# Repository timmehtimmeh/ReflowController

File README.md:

# TimmehTimmeh's Arduino Board

This repository contains support for the following TimmehTimmeh Arduino-compatible reflow oven controller.  The reflow controller runs on an Atmega32u4 at 3.3V/8MHz.

# Attributions
This project is based on TMK's headless reflow oven (https://github.com/tmk/HeadlessReflowOven) which is in turn based on  work of 

* [ohararp ReflowOven]  (https://github.com/ohararp/ReflowOven)

* which is modification of [rocketscream Reflow-Oven-Controller]  (https://github.com/rocketscream/Reflow-Oven-Controller)

rocketscream released the work under Creative Commons Share Alike v3.0 license.

The bootloader and corresponding installation instructions are a modification of Sparkfun's bootloader code for their Arduino Pro Micro: (https://github.com/sparkfun/Arduino_Boards)

The directory structure is as follows:
* [ReflowBoard]	- The firmware, bootloader, and arduino IDE files that communicate with the board
* [ReflowOven]	- The software (arduino software project) that runs on the board
* [Schematics] - schematics and eagle files for the board
* [libraries] - Library files that the arduino project links against

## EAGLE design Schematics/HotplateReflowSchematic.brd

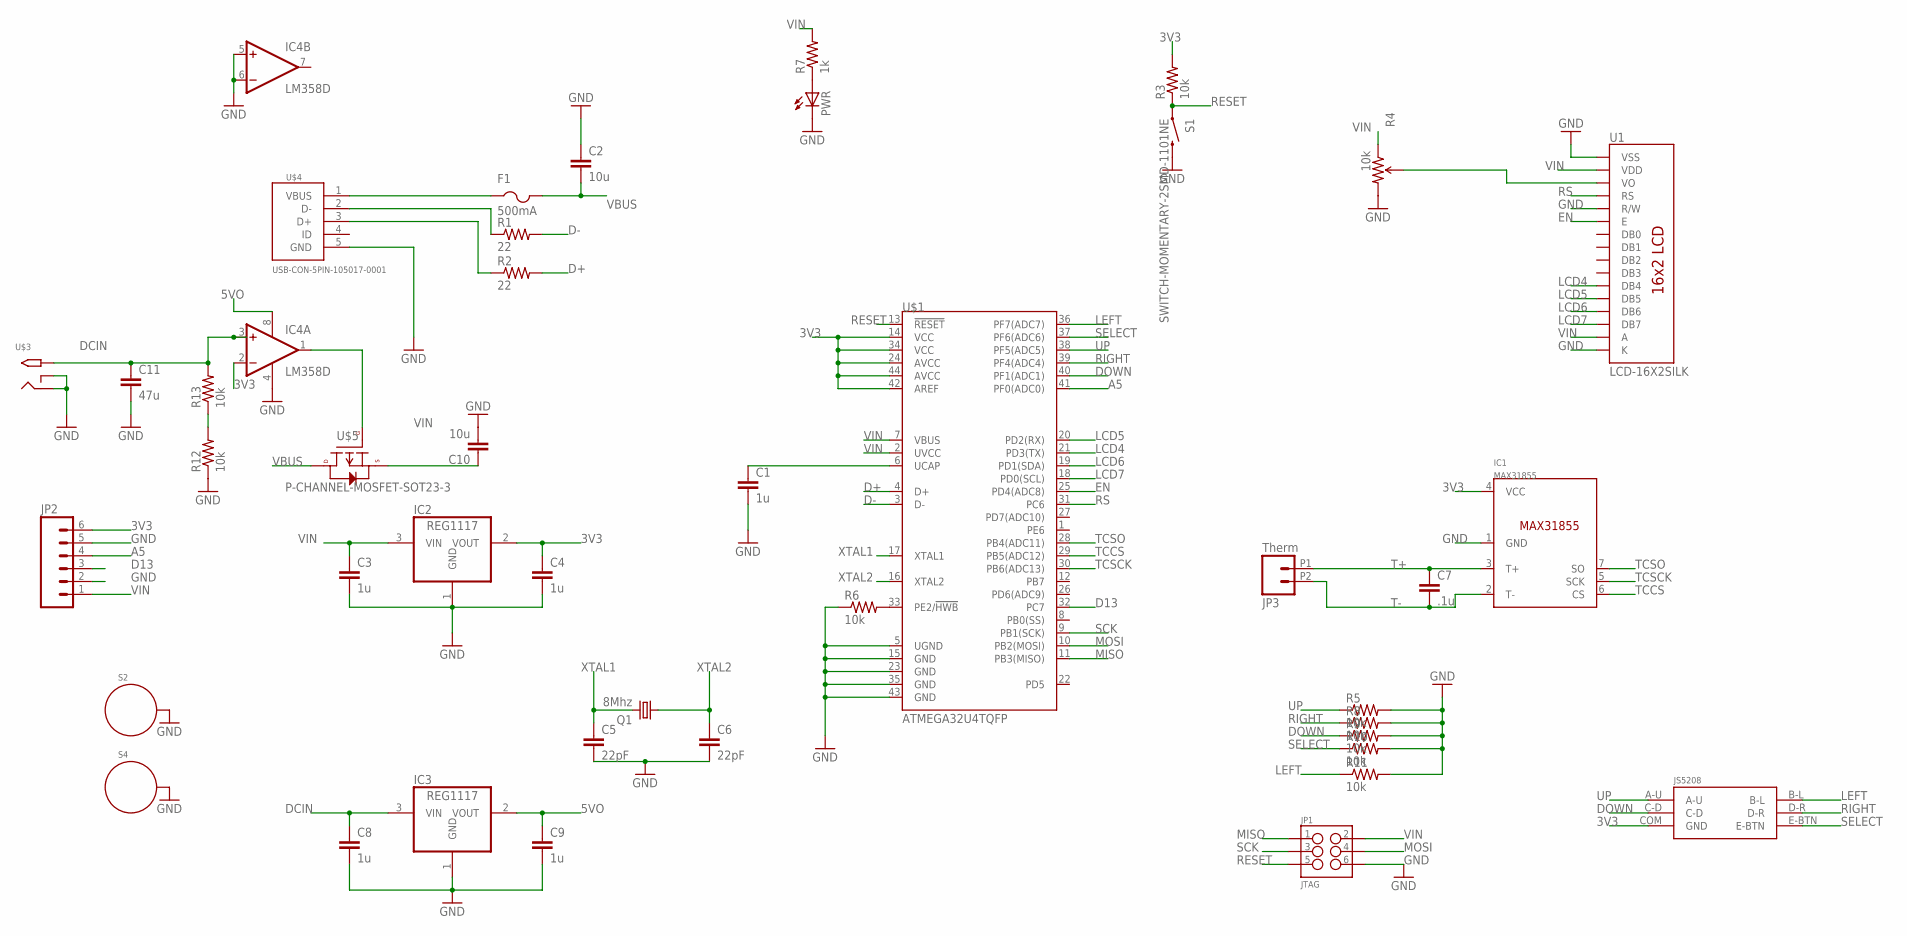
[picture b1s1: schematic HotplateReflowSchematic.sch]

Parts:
C1, C3, C4, C8, C9: 1u; 0603-CAP
C2, C10: 10u; 0603-CAP
C5, C6: 22pF; 0603-CAP
C7: .1u; 0603-CAP
C11: 47u; 0603-CAP
F1: 500mA; 1812
IC1: MAX31855; SOIC8
IC2, IC3: REG1117; SOT223
IC4: LM358D; SO08
JP1: JTAG; 2X3-SHROUDED
JP2: M06LOCK; 1X06_LOCK
JP3: Therm; 1X02_2.54_SCREWTERM
PWR: LEDCHIP-LED0603; CHIP-LED0603
Q1: 8Mhz; HC49UP
R1, R2: 22; 0603-RES
R3, R5, R6, R8, R9, R10, R11, R12, R13: 10k; 0603-RES
R4: 10k; TRIMPOT-5MM-V2
R7: 1k; 0603-RES
S1: SWITCH-MOMENTARY-2SMD-1101NE; TACTILE-SWITCH-1101NE
S2, S4: STANDOFF_ELECTRICAL; STANDOFF-ELECTRICAL
U1: LCD-16X2SILK; LCD-16X2
U$1: ATMEGA32U4TQFP; SPARKFUN-DIGITALIC_TQFP44
U$2: JS5208; JS5208_PKG
U$3: 2.1MMJACKTHM; PJ-102A
U$4: USB-CON-5PIN-105017-0001; USB-MICRO-MOLEX-105017-0001
U$5: P-CHANNEL-MOSFET-SOT23-3; SOT23-3

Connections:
3V3: C4.1, IC1.4 (VCC), IC2.2 (VOUT), IC4.2 (-IN), JP2.6, R3.2, U$1.14 (VCC), U$1.24 (AVCC), U$1.34 (VCC), U$1.42 (AREF), U$1.44 (AVCC), U$2.COM (GND)
5VO: C9.1, IC3.2 (VOUT), IC4.8 (V+)
A5: JP2.4, U$1.41 (PF0(ADC0))
D13: JP2.3, U$1.32 (PC7)
D+: R2.2, U$1.4 (D+)
D-: R1.2, U$1.3 (D-)
DCIN: C8.1, C11.1, IC3.3 (VIN), IC4.3 (+IN), R13.2, U$3.TIP
DOWN: R9.1, U$1.40 (PF1(ADC1)), U$2.C-D
EN: U1.6 (E), U$1.25 (PD4(ADC8))
GND: C1.2, C2.1, C3.2, C4.2, C5.2, C6.2, C8.2, C9.2, C10.2, C11.2, IC1.1 (GND), IC2.1 (GND), IC3.1 (GND), IC4.4 (V-), IC4.5 (+IN), IC4.6 (-IN), JP1.6, JP2.2, JP2.5, PWR.C, R4.C (CW), R5.2, R6.1, R8.2, R9.2, R10.2, R11.2, R12.1, S1.2, S2.P1, S4.P1, U1.1 (VSS), U1.5 (R/W), U1.16 (K), U$1.5 (UGND), U$1.15 (GND), U$1.23 (GND), U$1.35 (GND), U$1.43 (GND), U$3.RING, U$3.RING_SW, U$4.5 (GND)
LCD4: U1.11 (DB4), U$1.21 (PD3(TX))
LCD5: U1.12 (DB5), U$1.20 (PD2(RX))
LCD6: U1.13 (DB6), U$1.19 (PD1(SDA))
LCD7: U1.14 (DB7), U$1.18 (PD0(SCL))
LEFT: R11.1, U$1.36 (PF7(ADC7)), U$2.B-L
MISO: JP1.1, U$1.11 (PB3(MISO))
MOSI: JP1.4, U$1.10 (PB2(MOSI))
unnamed: R4.B (WIPER), U1.3 (VO)
unnamed: F1.1, U$4.1 (VBUS)
unnamed: R1.1, U$4.2 (D-)
unnamed: R2.1, U$4.3 (D+)
unnamed: C1.1, U$1.6 (UCAP)
unnamed: PWR.A, R7.1
unnamed: R6.2, U$1.33 (PE2/!HWB)
unnamed: R12.2, R13.1
unnamed: IC4.1 (OUT), U$5.1 (G)
RESET: JP1.5, R3.1, S1.1, U$1.13 (!RESET)
RIGHT: R8.1, U$1.39 (PF4(ADC4)), U$2.D-R
RS: U1.4 (RS), U$1.31 (PC6)
SCK: JP1.3, U$1.9 (PB1(SCK))
SELECT: R10.1, U$1.37 (PF6(ADC6)), U$2.E-BTN
T+: C7.1, IC1.3 (T+), JP3.P1 (1)
T-: C7.2, IC1.2 (T-), JP3.P2 (2)
TCCS: IC1.6 (CS), U$1.29 (PB5(ADC12))
TCSCK: IC1.5 (SCK), U$1.30 (PB6(ADC13))
TCSO: IC1.7 (SO), U$1.28 (PB4(ADC11))
UP: R5.1, U$1.38 (PF5(ADC5)), U$2.A-U
VBUS: C2.2, F1.2, U$5.3 (D)
VIN: C3.1, C10.1, IC2.3 (VIN), JP1.2, JP2.1, R4.A (CCW), R7.2, U1.2 (VDD), U1.15 (A), U$1.2 (UVCC), U$1.7 (VBUS), U$5.2 (S)
XTAL1: C5.1, Q1.2, U$1.17 (XTAL1)
XTAL2: C6.1, Q1.1, U$1.16 (XTAL2)

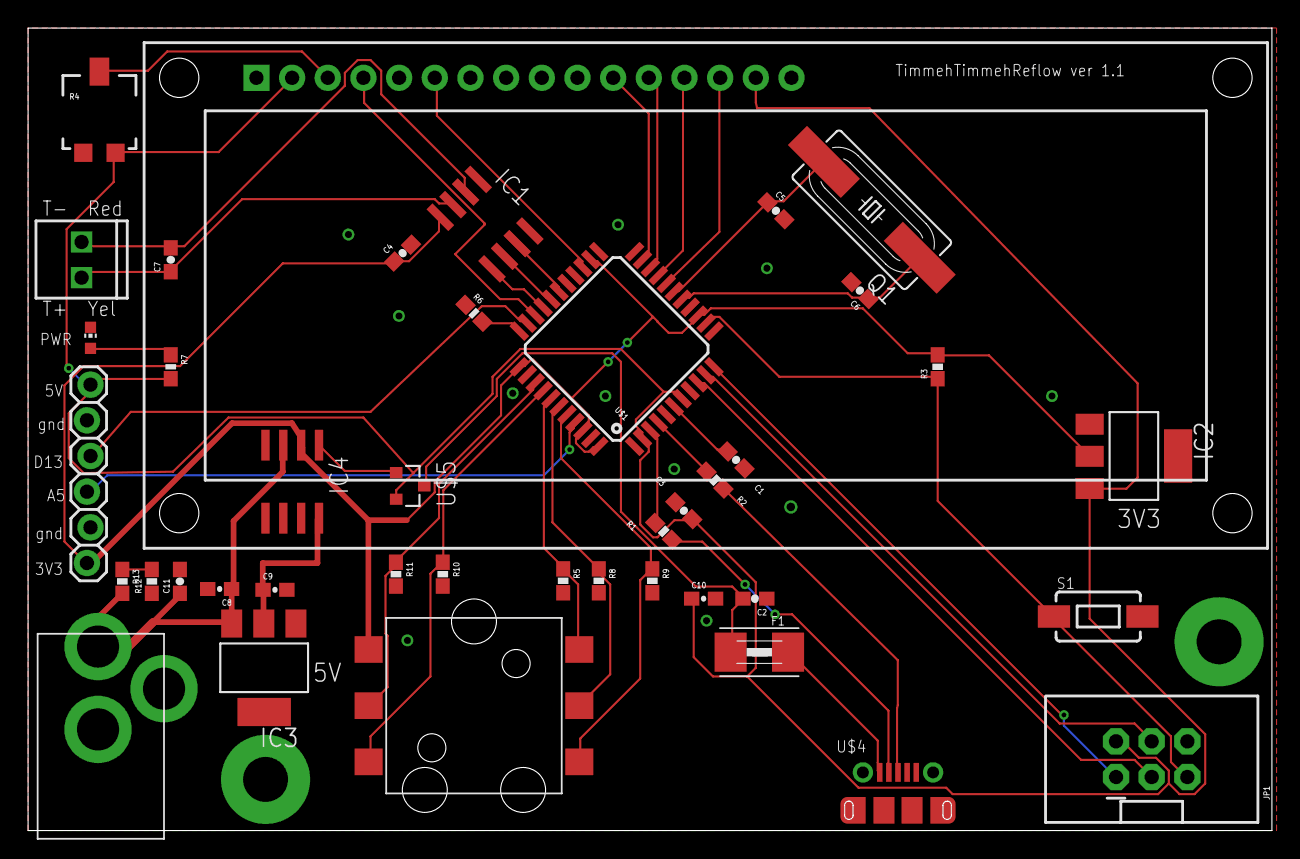
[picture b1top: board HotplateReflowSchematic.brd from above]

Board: 2 copper layers, 88.6 x 57.1 mm, 43 parts (0 on the bottom side), 41 nets.

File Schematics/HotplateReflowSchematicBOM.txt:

Partlist exported from C:/Users/timme/Documents/Arduino/ReflowController/Schematics/HotplateReflowSchematic.sch at 6/29/2016 9:49 PM

Qty Value                        Device                       Package                     Parts                              Description                                                                              MF MPN     OC_FARNELL OC_NEWARK PROD_ID   
1                                LEDCHIP-LED0603              CHIP-LED0603                PWR                                LED                                                                                                                                
1                                M06LOCK                      1X06_LOCK                   JP2                                Header 6                                                                                                                           
1   .1u                          CAP0603-CAP                  0603-CAP                    C7                                 Capacitor                                                                                                                          
1   10k                          RESISTOR0603                 0603-RES                    R6                                 Resistor                                                                                                                           
8   10k                          RESISTOR0603-RES             0603-RES                    R3, R5, R8, R9, R10, R11, R12, R13 Resistor                                                                                                                           
1   10k                          TRIMPOT                      TRIMPOT-5MM-V2              R4                                 Various small potentiometers for "set-and-forget" applications                                                                     
2   10u                          CAP0603-CAP                  0603-CAP                    C2, C10                            Capacitor                                                                                                                          
1   1k                           RESISTOR0603                 0603-RES                    R7                                 Resistor                                                                                                                           
5   1u                           CAP0603-CAP                  0603-CAP                    C1, C3, C4, C8, C9                 Capacitor                                                                                                                          
1   2.1MMJACKTHM                 2.1MMJACKTHM                 PJ-102A                     U$3                                2.1mm x 5.5mm THM DC jack with internal switch. Digikey part #PJ-102A, 4UCON part #05537                                           
2   22                           RESISTOR0603-RES             0603-RES                    R1, R2                             Resistor                                                                                                                           
2   22pF                         CAP0603-CAP                  0603-CAP                    C5, C6                             Capacitor                                                                                                                          
1   47u                          CAP0603-CAP                  0603-CAP                    C11                                Capacitor                                                                                                                          
1   500mA                        PTCFUSE-1812                 1812                        F1                                 PTC fuses, resettable thermistors                                                                                                  
1   8Mhz                         CRYSTALHC49UP                HC49UP                      Q1                                 CRYSTAL                                                                                             unknown    unknown             
1   ATMEGA32U4TQFP               ATMEGA32U4TQFP               SPARKFUN-DIGITALIC_TQFP44   U$1                                Atmel 44-pin 8-bit Microcontroller with 32KBytes of ISP Flash and USB Controller -----                                   IC-11161  
1   JS5208                       JS5208                       JS5208_PKG                  U$2                                                                                                                                                                   
1   JTAG                         M03X2SHROUD                  2X3-SHROUDED                JP1                                2x3 .1" header.                                                                                                          CONN-10681
1   LCD-16X2SILK                 LCD-16X2SILK                 LCD-16X2                    U1                                 Standard text-only 16x2 parallel input LCD                                                                                         
1   LM358D                       LM358D                       SO08                        IC4                                OP AMP also LM158; LM258; LM2904                                                                                                   
1   MAX31855                     MAX31855                     SOIC8                       IC1                                                                                                                                                                   
1   P-CHANNEL-MOSFET-SOT23-3     P-CHANNEL-MOSFET-SOT23-3     SOT23-3                     U$5                                P-Channel MOSFET Mode Field Effect Transistor                                                                                      
2   REG1117                      REG1117                      SOT223                      IC2, IC3                           800mA and 1A Low Dropout (LDO) Positive Regulator                                           REG1117 1097566    14P6981             
2   STANDOFF_ELECTRICAL          STANDOFF_ELECTRICAL          STANDOFF-ELECTRICAL         S2, S4                             A standoff intended to be an electrically connected point.                                                                         
1   SWITCH-MOMENTARY-2SMD-1101NE SWITCH-MOMENTARY-2SMD-1101NE TACTILE-SWITCH-1101NE       S1                                 Various NO switches- pushbuttons, reed, etc                                                                              SWCH-00815
1   Therm                        M022.54MM_SCREWTERM          1X02_2.54_SCREWTERM         JP3                                Standard 2-pin 0.1" header. Use with                                                                                               
1   USB-CON-5PIN-105017-0001     USB-CON-5PIN-105017-0001     USB-MICRO-MOLEX-105017-0001 U$4                                Molex Micro USB 105017-0001

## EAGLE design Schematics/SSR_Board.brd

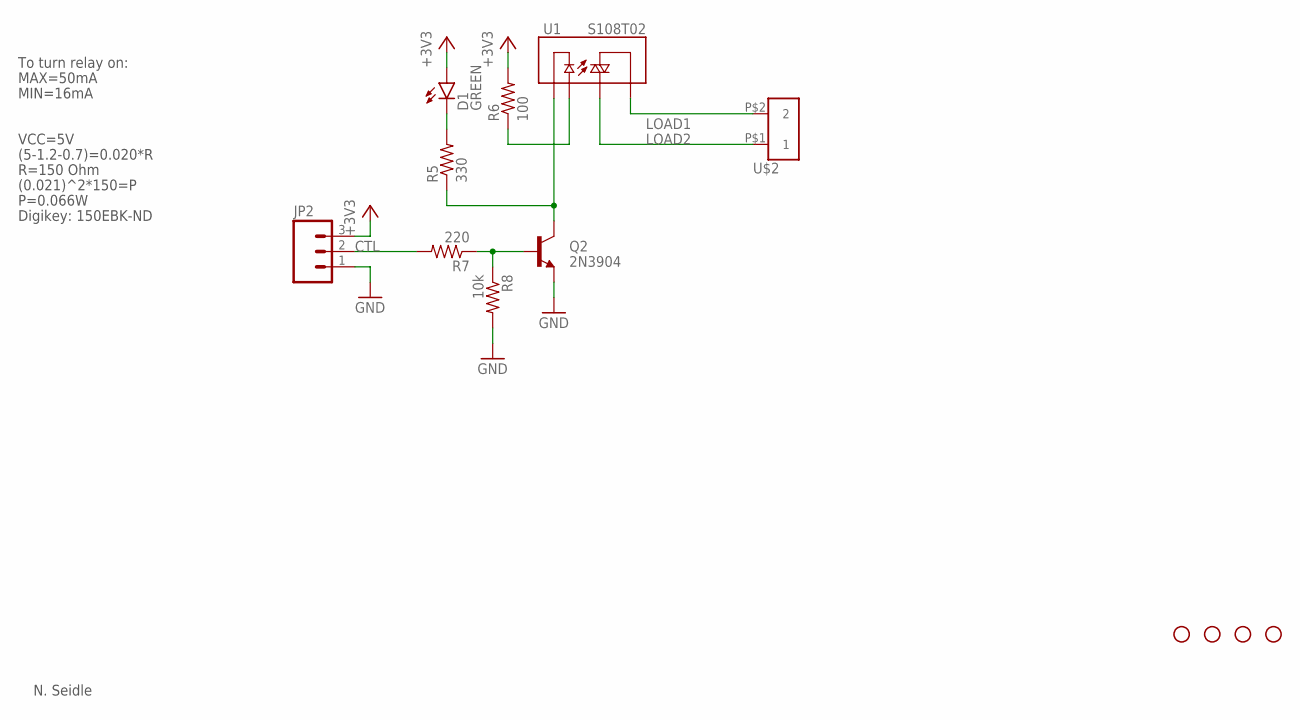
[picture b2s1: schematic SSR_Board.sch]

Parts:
D1: GREEN; LED-0603
JP2: M03SCREW; SCREWTERMINAL-3.5MM-3
Q2: 2N3904; SOT23-3
R5: 330; 0603-RES
R6: 100; 0603-RES
R7: 220; 0603-RES
R8: 10k; 0603-RES
U1: S108T02; RELAY-S108T02
U$2: 6PCV-02-006
U$3, U$4, U$5, U$7: STAND-OFF

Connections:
+3V3: D1.A, JP2.3, R6.2
COIL: Q2.3 (C), R5.1, U1.4 (-)
CTL: JP2.2, R7.2
GND: JP2.1, Q2.2 (E), R8.2
LOAD1: U1.1 (T1), U$2.P$2 (2)
LOAD2: U1.2 (T2), U$2.P$1 (1)
unnamed: R6.1, U1.3 (+)
unnamed: Q2.1 (B), R7.1, R8.1
unnamed: D1.C, R5.2

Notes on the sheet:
N. Seidle
To turn relay on:
(5-1.2-0.7)=0.020*R
R=150 Ohm
VCC=5V
MAX=50mA
MIN=16mA
(0.021)^2*150=P
P=0.066W
Digikey: 150EBK-ND

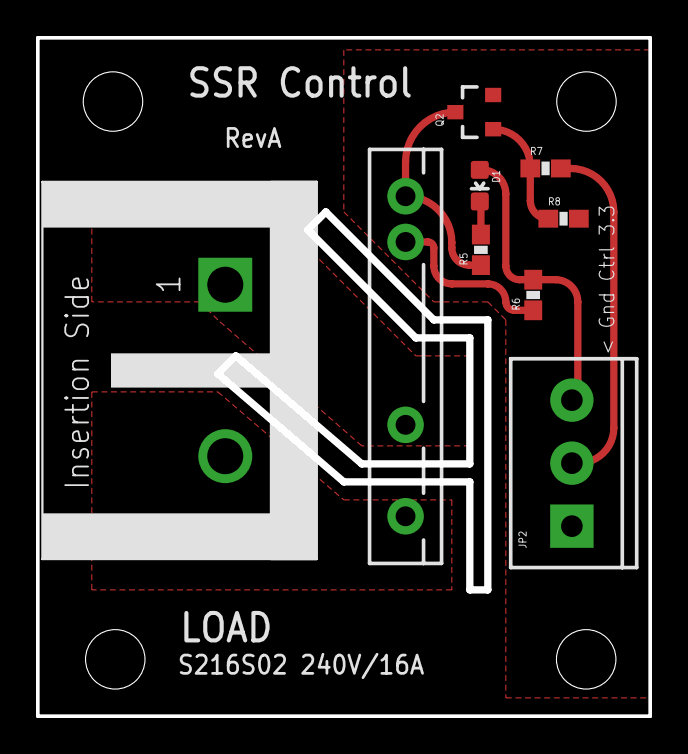
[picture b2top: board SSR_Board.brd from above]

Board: 2 copper layers, 33.8 x 37.5 mm, 13 parts (0 on the bottom side), 9 nets.

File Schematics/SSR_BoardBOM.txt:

Partlist exported from C:/Users/timme/Documents/Arduino/ReflowController/Schematics/SSR_Board.sch at 6/28/2016 10:34 PM

Qty Value       Device                Package               Parts              Description                    PROD_ID     VALUE
1               M03SCREW              SCREWTERMINAL-3.5MM-3 JP2                Header 3                                        
1   100         RESISTOR0603-RES      0603-RES              R6                 Resistor                                        
1   10k         RESISTOR0603-RES      0603-RES              R8                 Resistor                                        
1   220         RESISTOR0603-RES      0603-RES              R7                 Resistor                                        
1   2N3904      TRANSISTOR_NPNSOT23-3 SOT23-3               Q2                 Generic NPN BJT                TRANS-08049      
1   330         RESISTOR0603-RES      0603-RES              R5                 Resistor                                        
1   6PCV-02-006 6PCV-02-006           6PCV-02-006           U$2                TE-Connectivity-AMP-Connectors                  
1   GREEN       LED-GREEN0603         LED-0603              D1                 Various green LEDs             DIO-00821   GREEN
1   S108T02     RELAY-SOLIDSTATEPTH   RELAY-S108T02         U1                                                                 
4   STAND-OFF   STAND-OFF             STAND-OFF             U$3, U$4, U$5, U$7 Stand Off

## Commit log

2016-06-28 Add files via upload
    Making menu code make better use of joystick
2016-06-29 Removing duplicated libraries
2016-06-29 removing thumbs.db
2016-06-29 Changing display to Celsius to align with reflow profiles
2016-06-29 fixing silkscreen on board for power switch
2016-06-29 adding temporary eagle files to .gitignore
2016-06-29 cleaning up some redundant menu code, and making delay between reading temps in menu mode
2016-06-29 Adding schematic for SSR control board. Renaming BOM file to be more obvious
2016-06-30 Updating schematic to have automatic switching between USB and DC jack
2016-07-13 Add files via upload
    adding SSR Board Schematic
2016-07-30 Add files via upload
    adding pdf of board layout
2016-07-30 Add files via upload
    adding ReflowController layout pdf

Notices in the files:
parts and their libraries:
SparkFun-Passives: Licensing: Creative Commons ShareAlike 4.0 International - https://creativecommons.org/licenses/by-sa/4.0
